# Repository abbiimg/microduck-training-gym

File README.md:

# MicroDuck training gym and design assets

Private working snapshot prepared on **2026-11-01**. This repository contains
MicroDuck CAD, PCB recovery projects, component models, simulation/training
artifacts, audit evidence, and four reusable personal skills.

## Start here

- [Latest package and remaining gaps](MODEL-PLACEMENT-PROGRESS.txt)
- [End-to-end status](END-TO-END-STATUS.txt)
- [17-stage software-check evidence](audit/pcb-tools/software-stack-result.json)
- [Recorded Isaac training run](simulation/validation-runs/2026-10-26_14-57-39_pcb_pipeline_baseline/validation.json)

Recorded checks are dated evidence from the source workstation. The bounded
Isaac run proves integration; it does not establish a reliable walking policy.
Manufacturing and physical reproduction remain unqualified. The canonical
XL330/Feetech choice and revised-IMU copper recovery remain open.

## Clone the published assets

GitHub Desktop supports this repository's Git LFS files. For command-line Git:

```sh
git lfs install
git clone <this-repository-url>
cd microduck-training-gym
git lfs pull
python tools/verify_publication.py
```

Use a Git/LFS clone rather than relying on GitHub's source ZIP. LFS stores CAD,
meshes, archives, media and policy weights separately from their Git pointers.
See [GitHub's LFS documentation](https://docs.github.com/en/repositories/working-with-files/managing-large-files/about-git-large-file-storage).

## Editing and reuse

- `editing/kicad-models-attached/`: five native KiCad review projects with local
  footprint models, assembly STEP/GLB exports and Blender review scenes. Keep
  each complete folder together; models use `${KIPRJMOD}` paths.
- `editing/kicad-cache-repaired/wire_hub_1V0A/`: separate engineering repair of
  the stale GND cache. This revision has no added 3D models; compare its audit.
- `editing/blender/`, `editing/solidworks/`, `community/SolidWorks-XL330-v1.1/`:
  robot meshes, exchange geometry and the community native CAD reconstruction.
- `simulation/`: USD assets and recorded training/export/replay evidence.
- `tools/`: recovery, generation and validation tools. Native KiCad/pcbnew,
  CadQuery/OCP, Blender and the documented WSL Isaac/PCB environments are
  separate prerequisites; their installed runtimes are not embedded here.
- `skills/`: MicroDuck, ECAD/MCAD, Blender/SolidWorks transfer and parametric
  CAD skills. Copy the desired folders into your personal skills directory and
  adapt machine-specific paths and application connections before reuse.

Tracked asset layout and payload bytes are preserved. Reviewed optional payloads are deferred as described below. Many historical scripts and
reports record absolute source-workstation paths. Consult the skill references
for the tested Windows ARM64 / WSL setup rather than assuming those paths exist
on a new machine. Review author/recovered frames before mechanical fit checks.

## Provenance and terms

Selected files from seven pinned source repositories are preserved as **plain file snapshots**, with their
original LICENSE/NOTICE files. [SOURCE-REPOSITORIES.json](SOURCE-REPOSITORIES.json)
records the original URLs and exact commits. Third-party terms remain attached
to each source; there is no blanket license for the whole collection. Robot
mesh derivatives include CC BY-NC-SA 4.0 material; some other source terms are
incomplete. Preserve notices and review rights before any public redistribution.

The original [asset-manifest.json](asset-manifest.json) remains historical
validation evidence, including entries for local caches and optional payloads
omitted from Git. [PUBLICATION-EXCLUSIONS.json](PUBLICATION-EXCLUSIONS.json) and
[DEFERRED-ASSETS.json](DEFERRED-ASSETS.json) document those omissions.
[PUBLICATION-MANIFEST.json](PUBLICATION-MANIFEST.json)
is the hash inventory for the files actually published in this snapshot.

All physical hardware operation, flashing and deployment require a separate
request and validation. No GitHub publication changes the package's recorded
hardware-readiness limits.

## Lean Git publication

See [GITIGNORE-REVIEW.md](GITIGNORE-REVIEW.md) and
[DEFERRED-ASSETS.json](DEFERRED-ASSETS.json). Original CAD release archives,
unused vendor models, optional Rufus binaries and regenerable duplicate exports
stay on the source workstation but are not included in this Git snapshot.
The 57 native working SolidWorks files, baseline Blender scene, current KiCad
model projects, source board STEP files, recovered component geometry, policy
artifacts and known 17-stage verification inputs remain included.

Restore exact deferred files from the retained full package when required:

```sh
python tools/restore_deferred_assets.py --source /path/to/microduck-assets
```

For the original author CAD release ZIP alone, this explicit command downloads
the recorded release and verifies its SHA256:

```sh
python tools/restore_deferred_assets.py --download-original-cad
```

The release ZIP is CAD-only (41 parts and 16 assemblies), with no SolidWorks
program or installer. Fifteen expanded working CAD files differ from that
release; its original URL/hash are retained so both versions remain recoverable.
Some optional export/build tools need deferred inputs restored or regenerated;
the current 17-stage verification receipts retain their known file inputs.

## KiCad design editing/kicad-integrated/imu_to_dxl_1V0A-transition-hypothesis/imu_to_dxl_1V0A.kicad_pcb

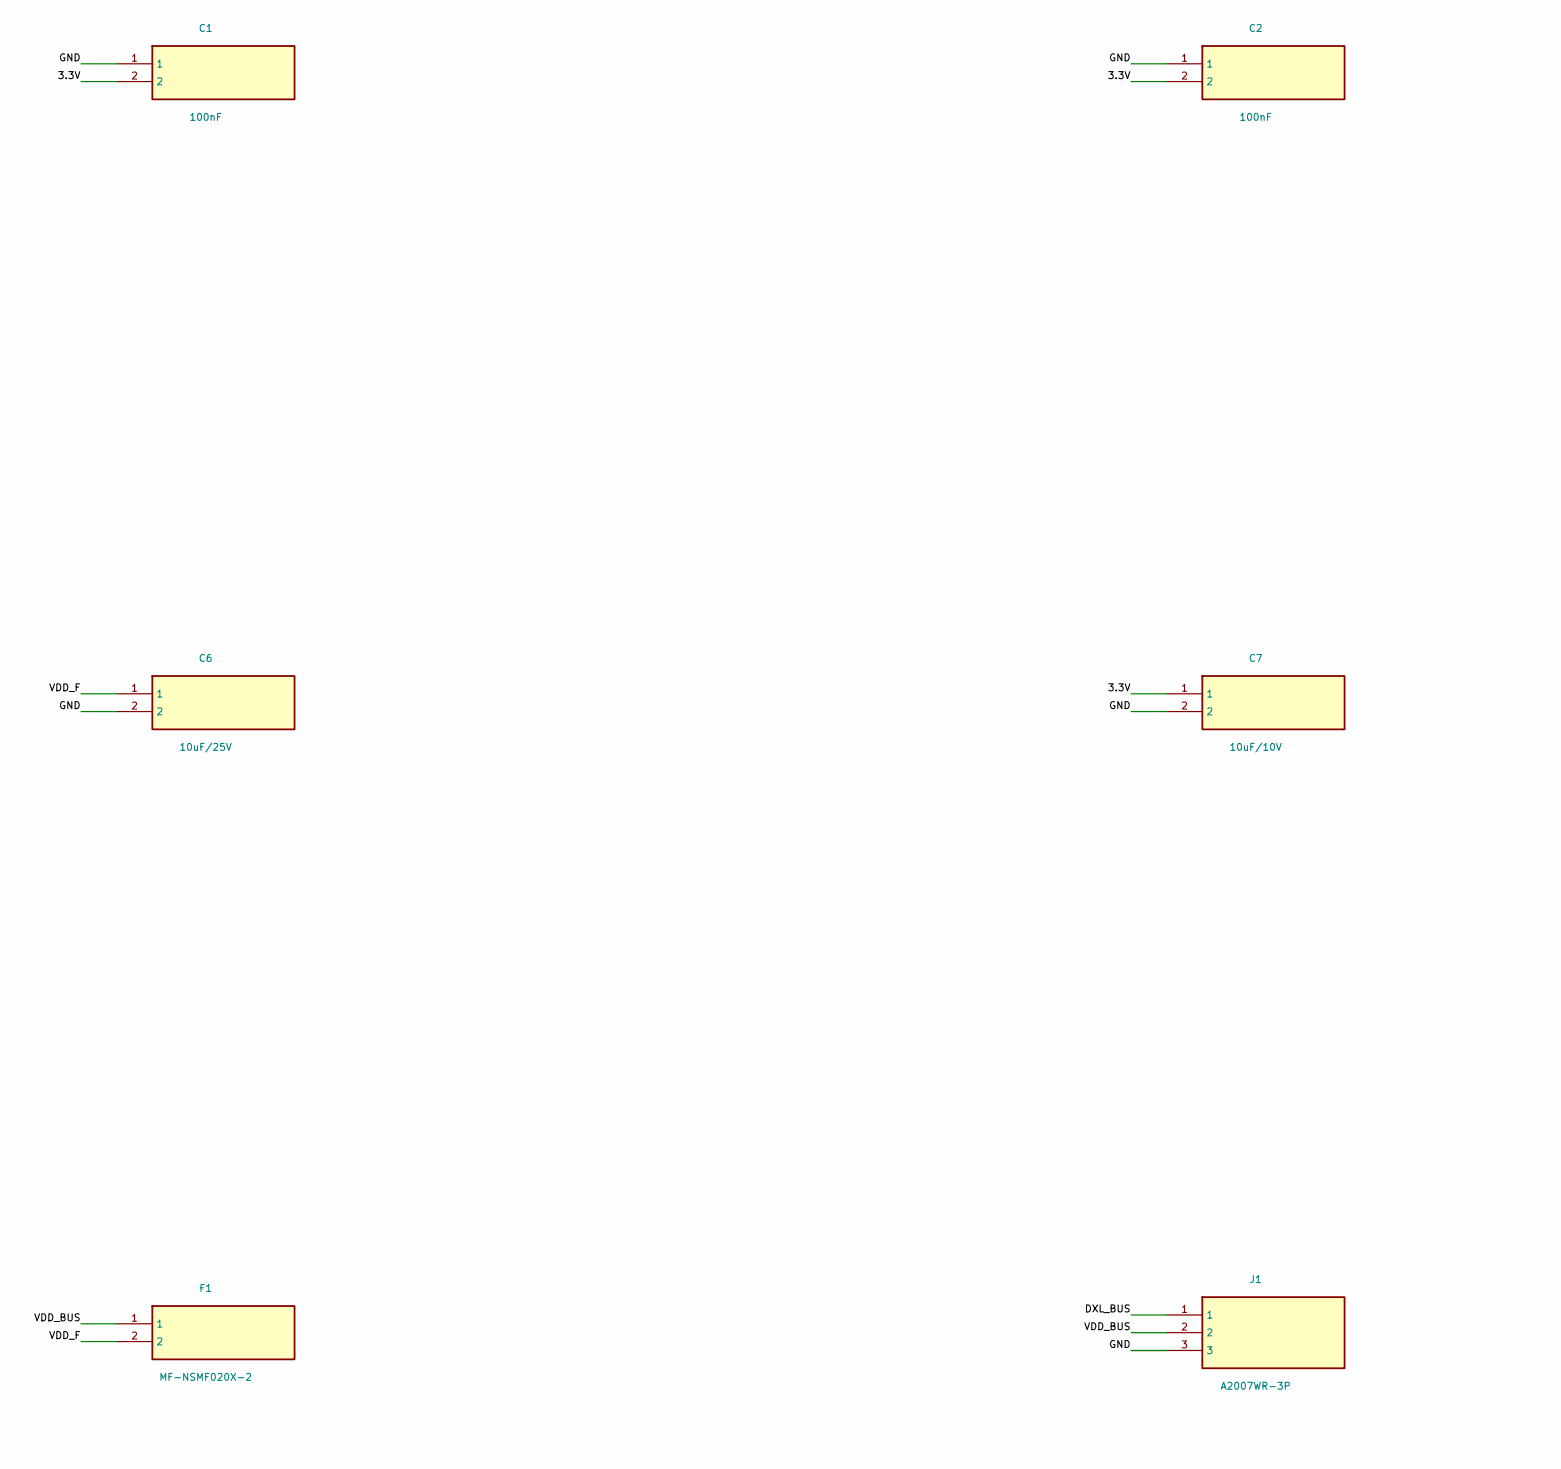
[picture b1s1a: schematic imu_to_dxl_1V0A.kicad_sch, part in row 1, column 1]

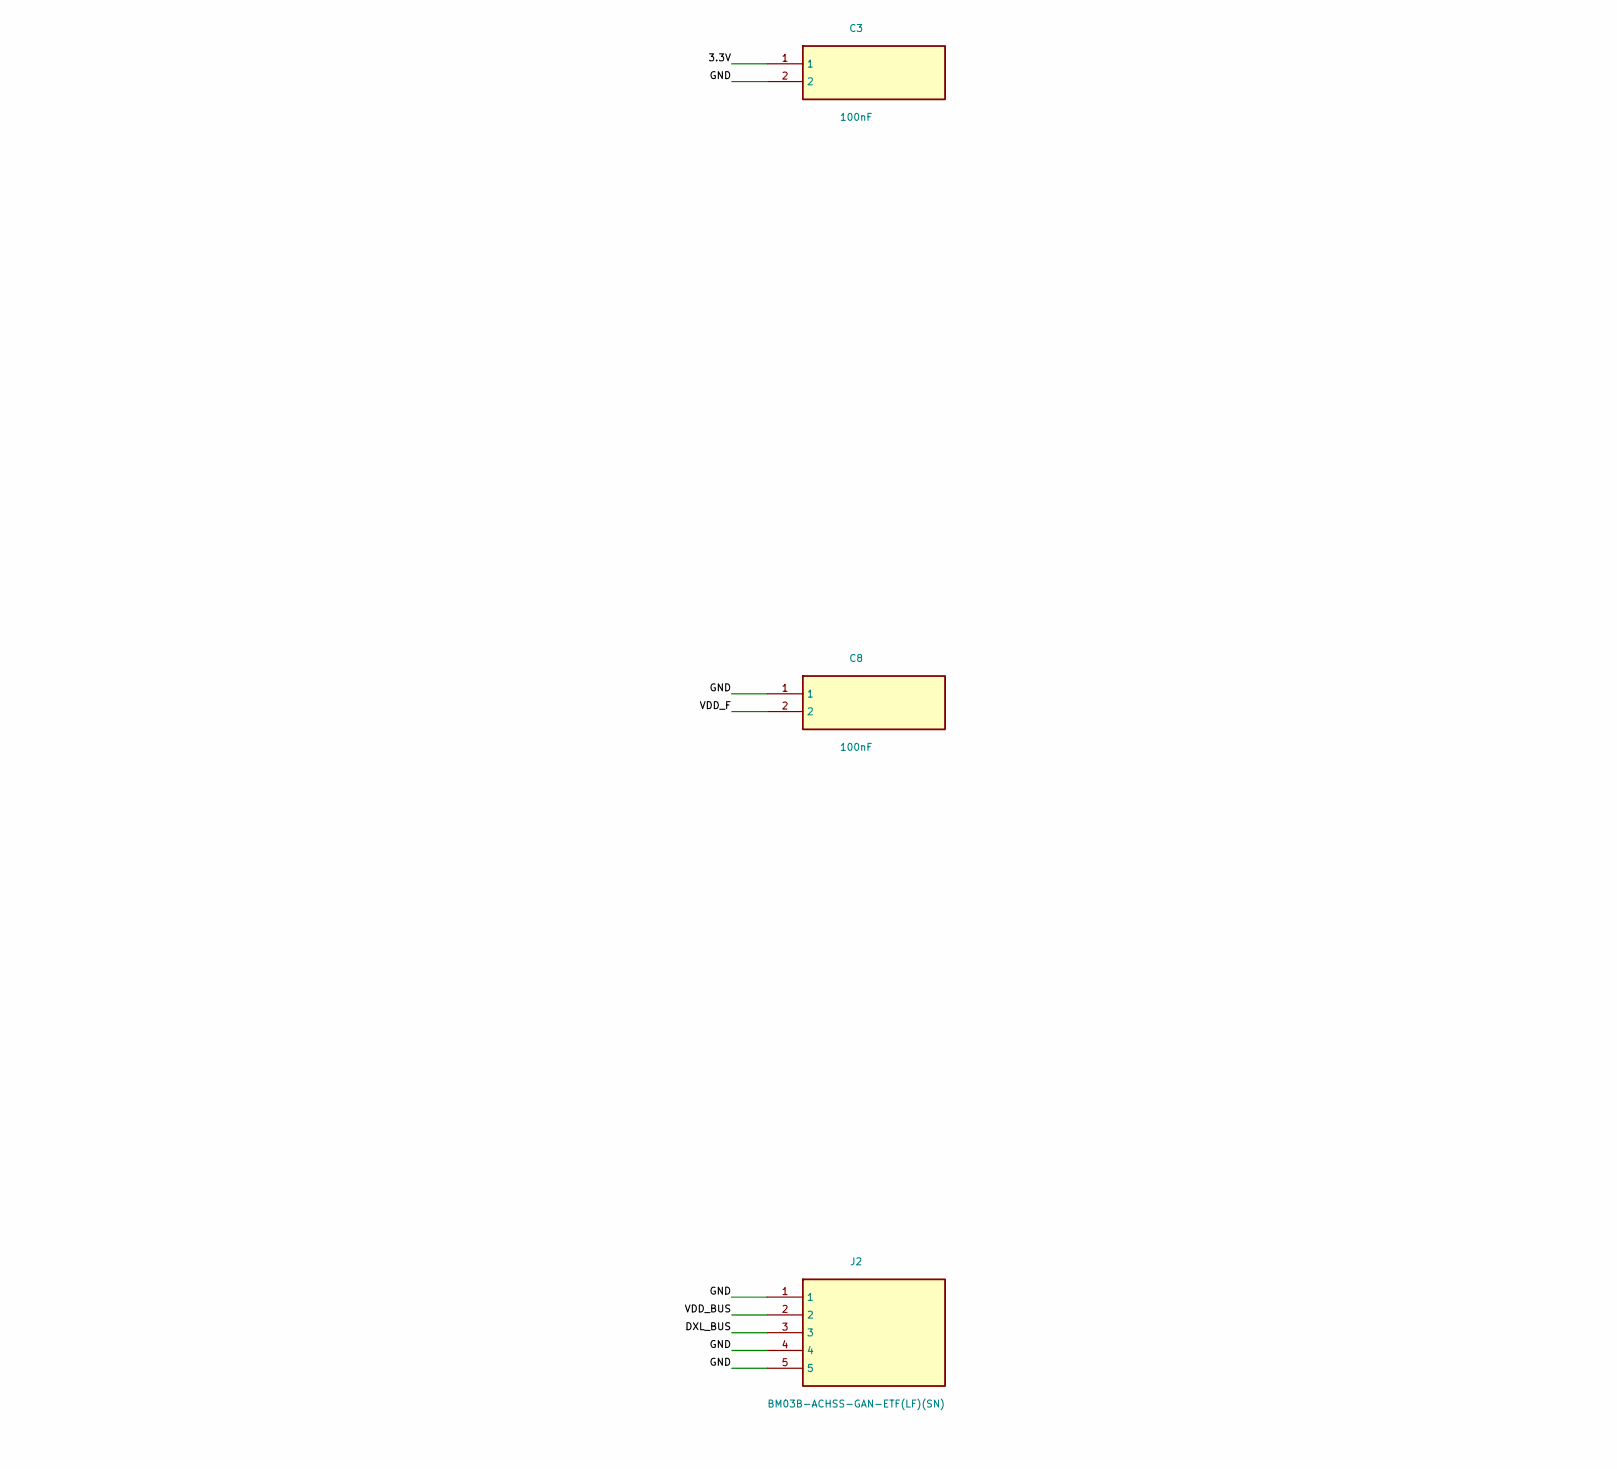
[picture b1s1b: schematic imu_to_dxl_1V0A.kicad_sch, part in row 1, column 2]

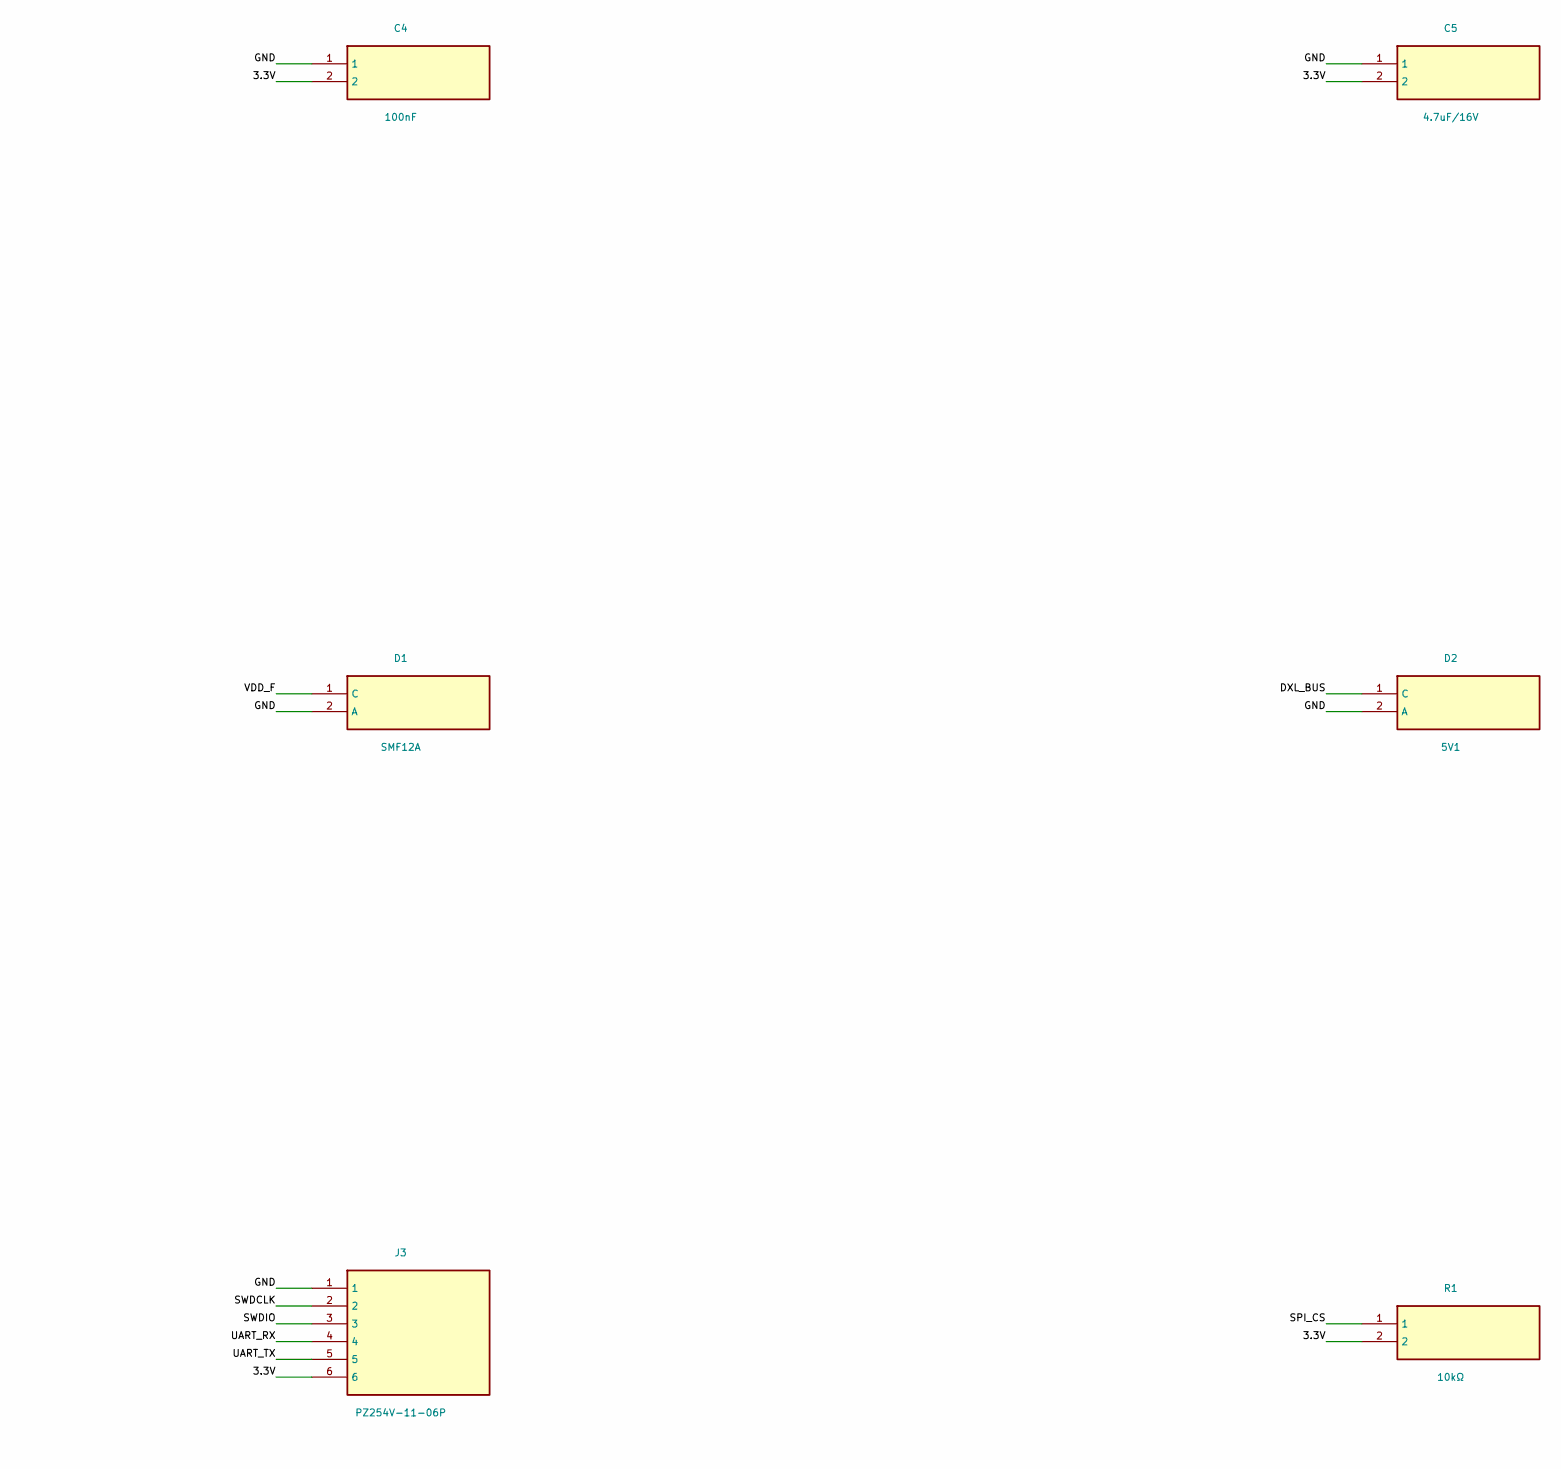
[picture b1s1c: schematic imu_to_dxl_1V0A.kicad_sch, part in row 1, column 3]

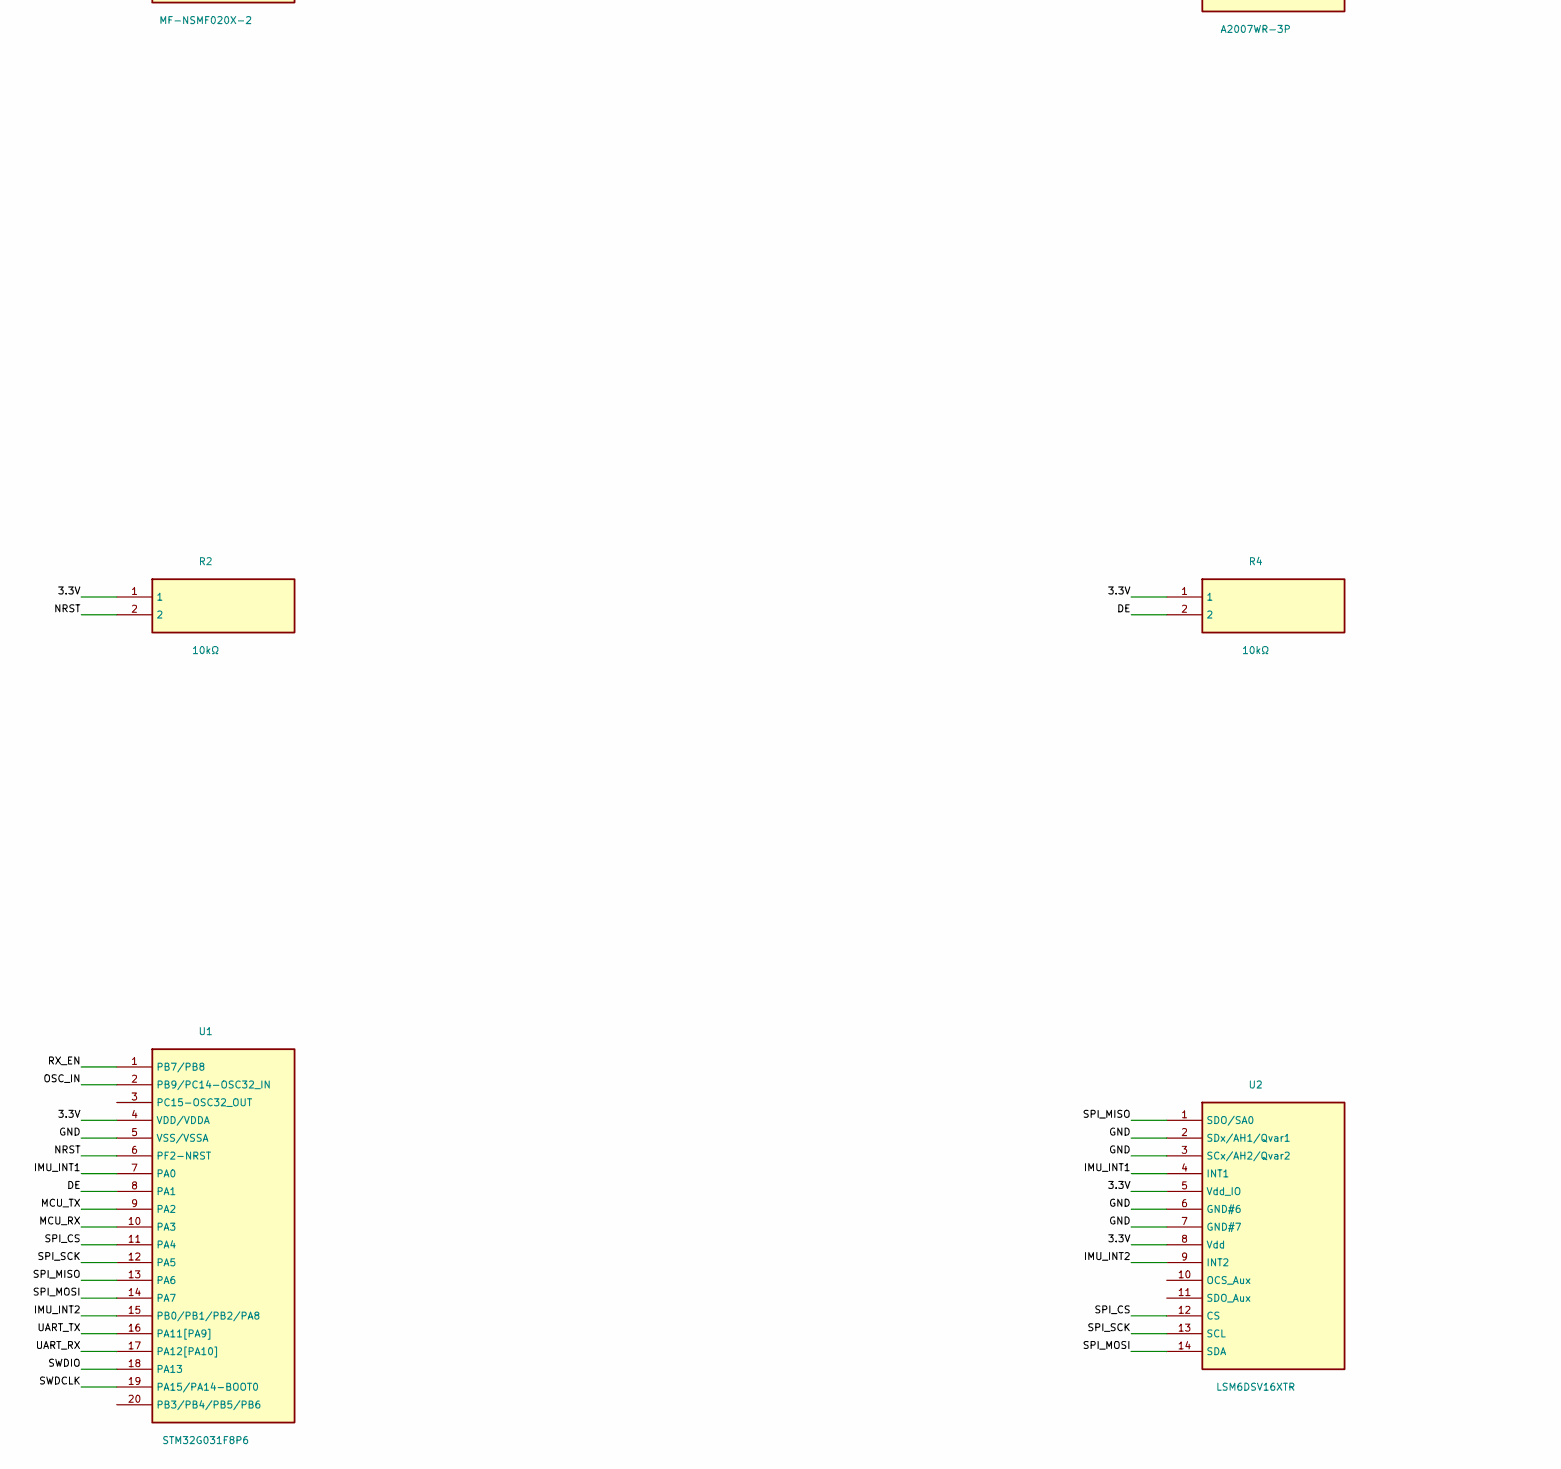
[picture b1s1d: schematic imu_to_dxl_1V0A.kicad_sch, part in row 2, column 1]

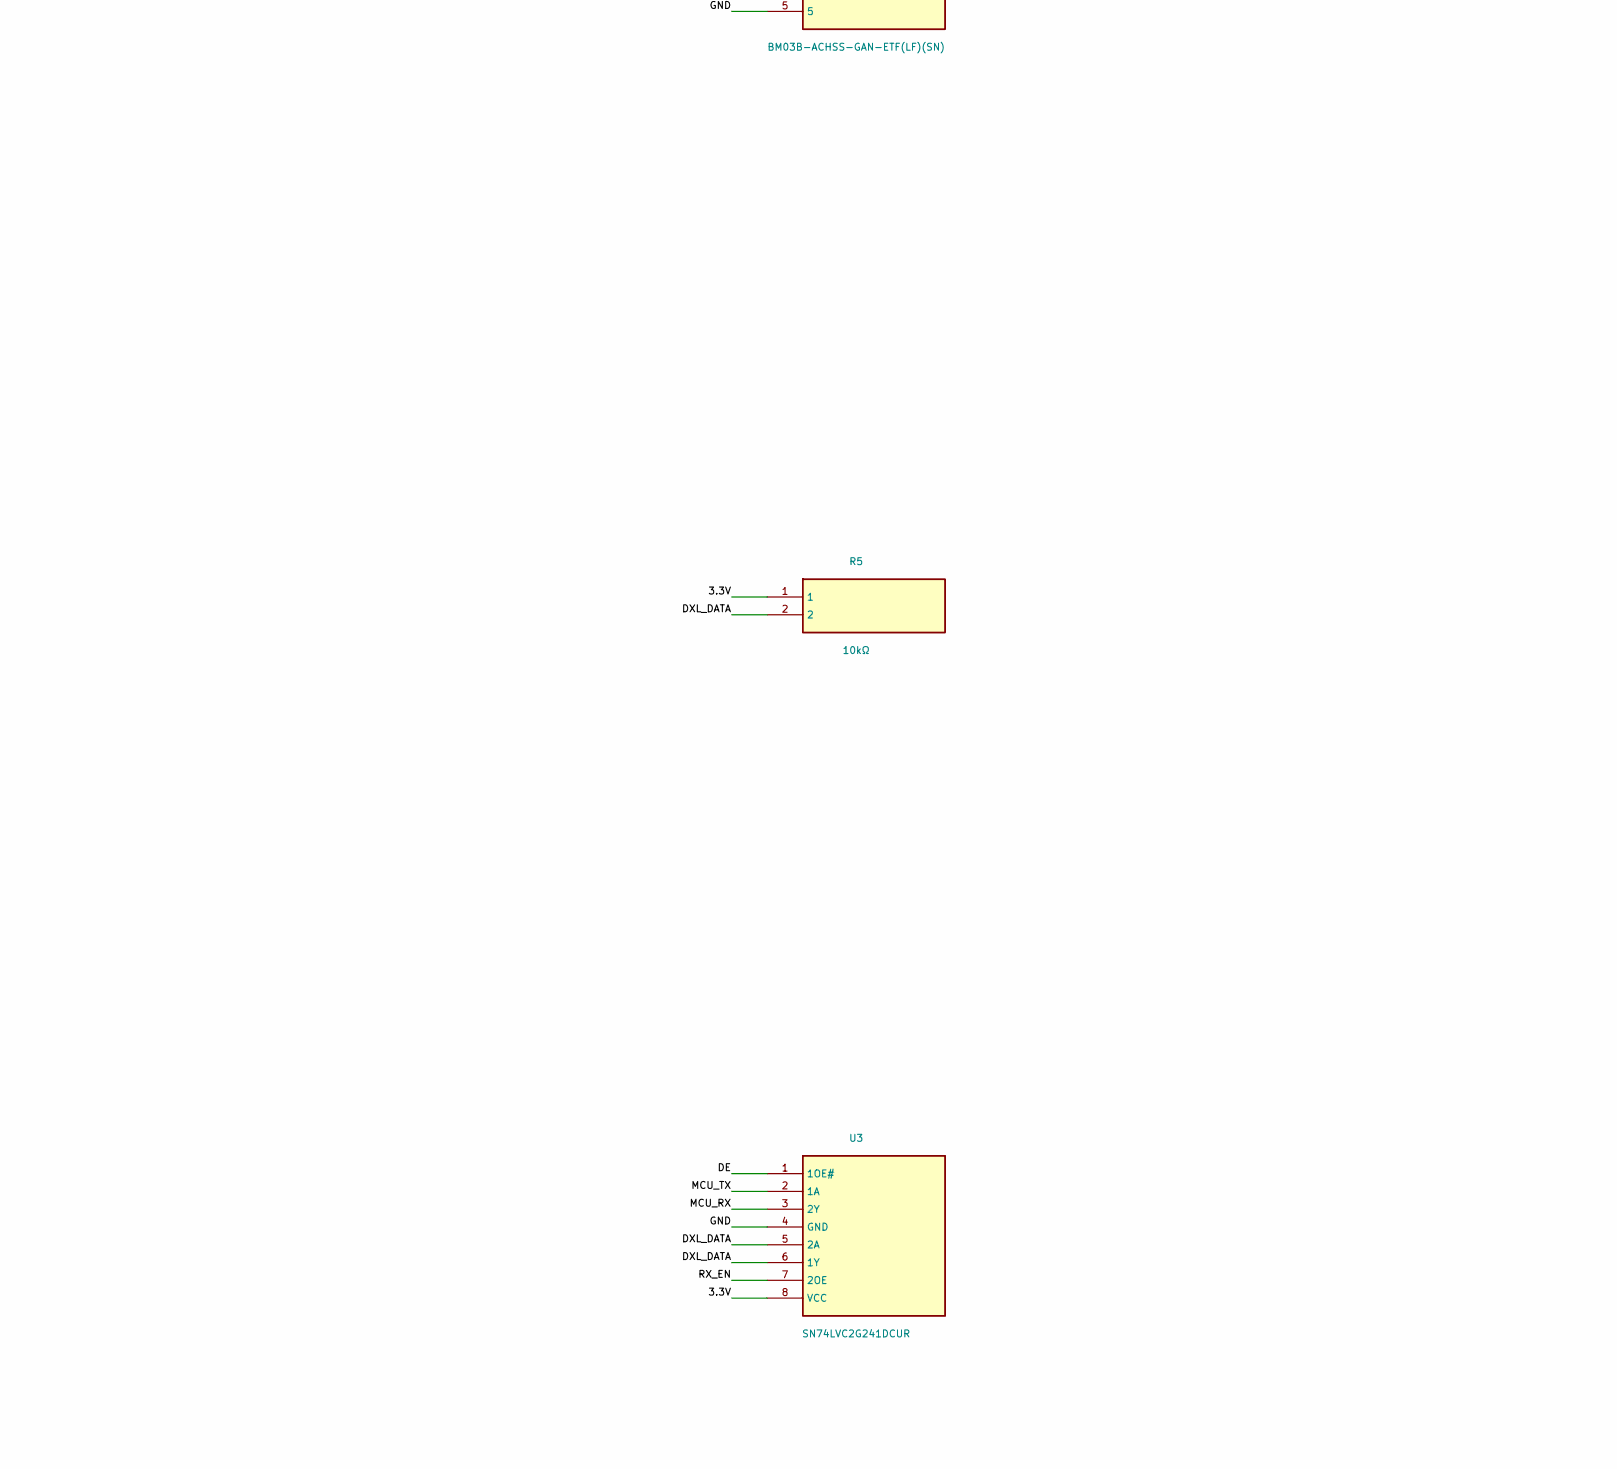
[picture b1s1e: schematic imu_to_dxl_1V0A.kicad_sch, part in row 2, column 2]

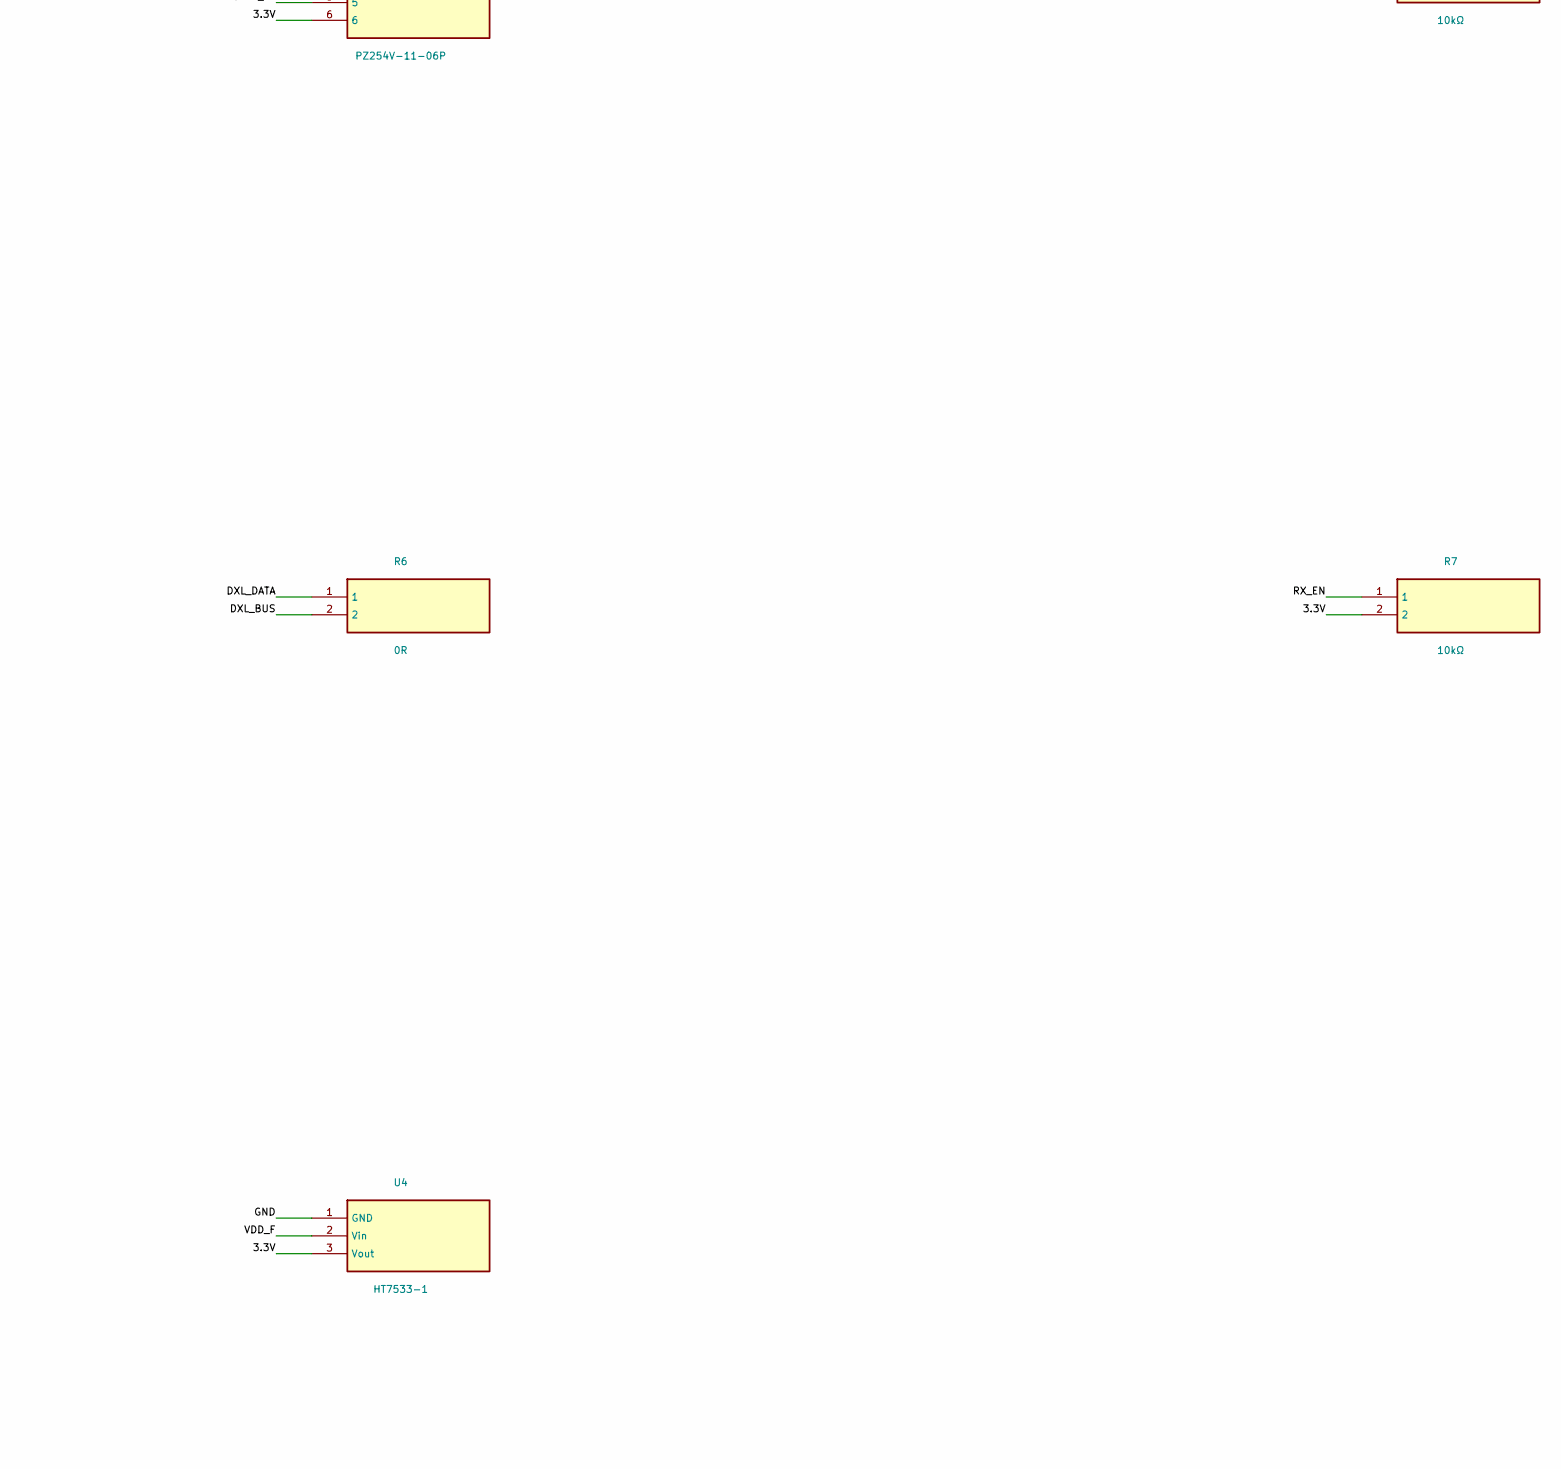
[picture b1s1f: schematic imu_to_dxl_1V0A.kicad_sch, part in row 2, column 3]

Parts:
C1: 100nF; C1; Manufacturer Part CL05B104KO5NNNC; LCSC C1525
C2: 100nF; C2; Manufacturer Part CL05B104KO5NNNC; LCSC C1525
C3: 100nF; C3; Manufacturer Part CL05B104KO5NNNC; LCSC C1525
C4: 100nF; C4; Manufacturer Part CL05B104KO5NNNC; LCSC C1525
C5: 4.7uF/16V; C5; Manufacturer Part CL10A475KO8NNNC; LCSC C19666
C6: 10uF/25V; C6; Manufacturer Part CL21A106KAYNNNE; LCSC C15850
C7: 10uF/10V; C7; Manufacturer Part CL10A106KP8NNNC; LCSC C19702
C8: 100nF; C8; Manufacturer Part CL05B104KO5NNNC; LCSC C1525
D1: SMF12A; D1; Manufacturer Part SMF12A; LCSC C2943870
D2: 5V1; D2; Manufacturer Part BZT52C5V1-7-F; LCSC C151588
F1: MF-NSMF020X-2; F1; Manufacturer Part MF-NSMF020X-2; LCSC C210358
J1: A2007WR-3P; J1; Manufacturer Part A2007WR-3P; LCSC C225350
J2: BM03B-ACHSS-GAN-ETF(LF)(SN); J2; Manufacturer Part BM03B-ACHSS-GAN-ETF(LF)(SN); LCSC C5118705
J3: PZ254V-11-06P; J3; Manufacturer Part PZ254V-11-06P; LCSC C492405
R1: 10kΩ; R1; Manufacturer Part RC0402FR-0710KL; LCSC C60490
R2: 10kΩ; R2; Manufacturer Part RC0402FR-0710KL; LCSC C60490
R4: 10kΩ; R4; Manufacturer Part RC0402FR-0710KL; LCSC C60490
R5: 10kΩ; R5; Manufacturer Part RC0402FR-0710KL; LCSC C60490
R6: 0R; R6; Manufacturer Part 0603WAF0000T5E; LCSC C21189
R7: 10kΩ; R7; Manufacturer Part RC0402FR-0710KL; LCSC C60490
U1: STM32G031F8P6; U1; Manufacturer Part STM32G031F8P6; LCSC C529334
U2: LSM6DSV16XTR; U2; Manufacturer Part LSM6DSV16XTR; LCSC C5267406
U3: SN74LVC2G241DCUR; U3; Manufacturer Part SN74LVC2G241DCUR; LCSC C10430
U4: HT7533-1; U4; Manufacturer Part HT7533-1; LCSC C14289

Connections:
/3.3V: C1.2, C2.2, C3.1, C4.2, C5.2, C7.1, J3.6, R1.2, R2.1, R4.1, R5.1, R7.2, U1.4 (VDD/VDDA), U2.5 (Vdd_IO), U2.8 (Vdd), U3.8 (VCC), U4.3 (Vout)
/DE: R4.2, U1.8 (PA1), U3.1 (1OE#)
/DXL_BUS: D2.1 (C), J1.1, J2.3, R6.2
/DXL_DATA: R5.2, R6.1, U3.5 (2A), U3.6 (1Y)
/GND: C1.1, C2.1, C3.2, C4.1, C5.1, C6.2, C7.2, C8.1, D1.2 (A), D2.2 (A), J1.3, J2.1, J2.4, J2.5, J3.1, U1.5 (VSS/VSSA), U2.2 (SDx/AH1/Qvar1), U2.3 (SCx/AH2/Qvar2), U2.6 (GND#6), U2.7 (GND#7), U3.4 (GND), U4.1 (GND)
/IMU_INT1: U1.7 (PA0), U2.4 (INT1)
/IMU_INT2: U1.15 (PB0/PB1/PB2/PA8), U2.9 (INT2)
/MCU_RX: U1.10 (PA3), U3.3 (2Y)
/MCU_TX: U1.9 (PA2), U3.2 (1A)
/NRST: R2.2, U1.6 (PF2-NRST)
/OSC_IN: U1.2 (PB9/PC14-OSC32_IN)
/RX_EN: R7.1, U1.1 (PB7/PB8), U3.7 (2OE)
/SPI_CS: R1.1, U1.11 (PA4), U2.12 (CS)
/SPI_MISO: U1.13 (PA6), U2.1 (SDO/SA0)
/SPI_MOSI: U1.14 (PA7), U2.14 (SDA)
/SPI_SCK: U1.12 (PA5), U2.13 (SCL)
/SWDCLK: J3.2, U1.19 (PA15/PA14-BOOT0)
/SWDIO: J3.3, U1.18 (PA13)
/UART_RX: J3.4, U1.17 (PA12[PA10])
/UART_TX: J3.5, U1.16 (PA11[PA9])
/VDD_BUS: F1.1, J1.2, J2.2
/VDD_F: C6.1, C8.2, D1.1 (C), F1.2, U4.2 (Vin)

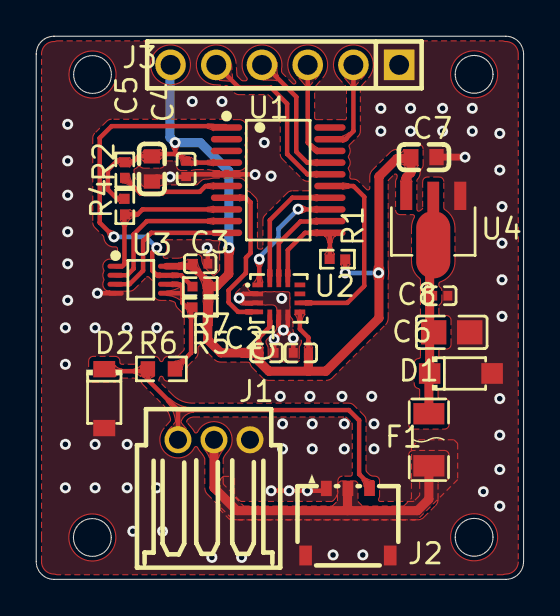
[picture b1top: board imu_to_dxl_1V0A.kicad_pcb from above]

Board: 2 copper layers, 27.1 x 30.2 mm, 24 parts (0 on the bottom side), 21 nets.

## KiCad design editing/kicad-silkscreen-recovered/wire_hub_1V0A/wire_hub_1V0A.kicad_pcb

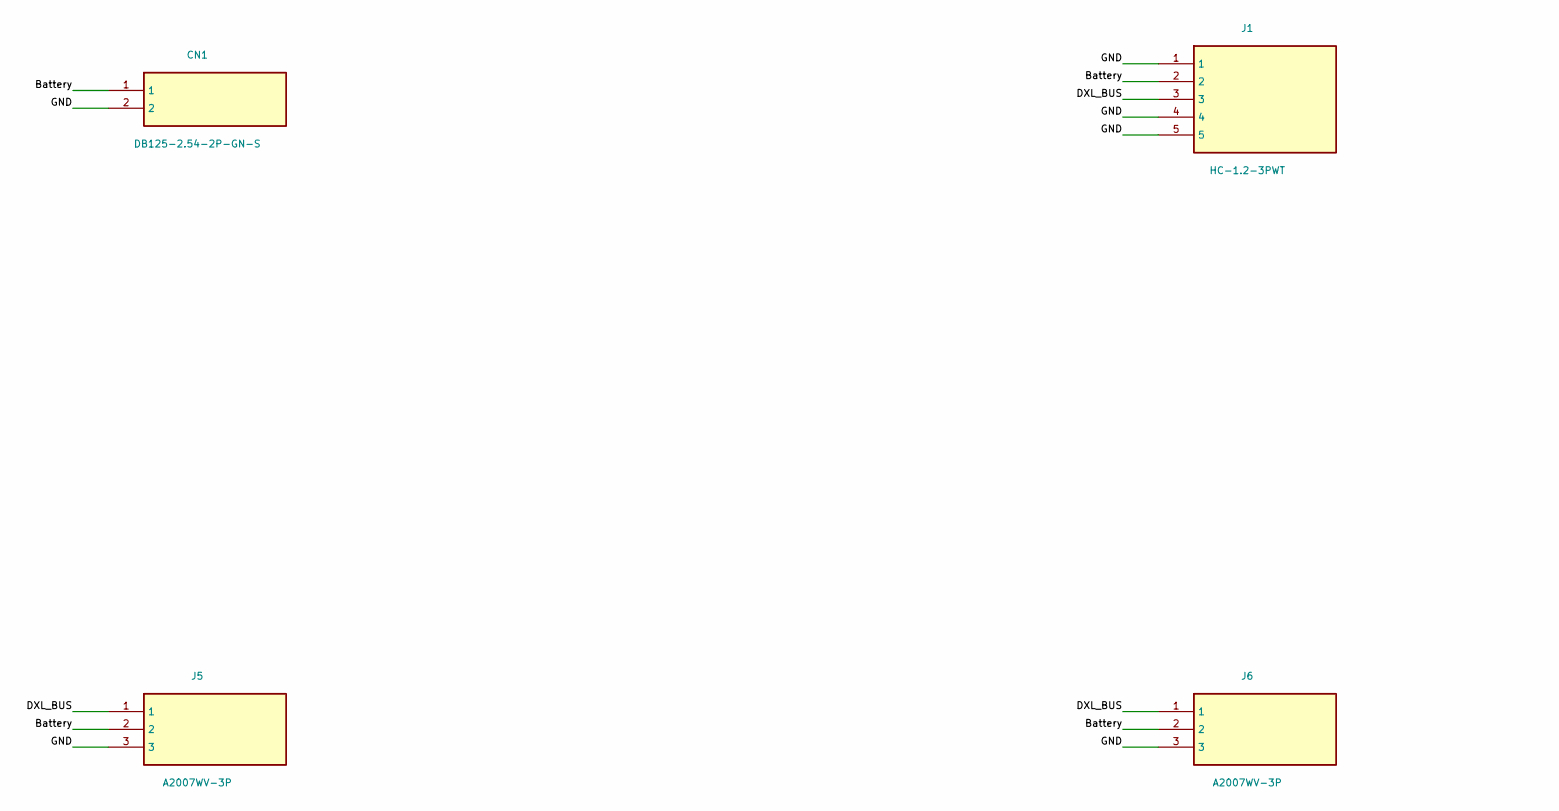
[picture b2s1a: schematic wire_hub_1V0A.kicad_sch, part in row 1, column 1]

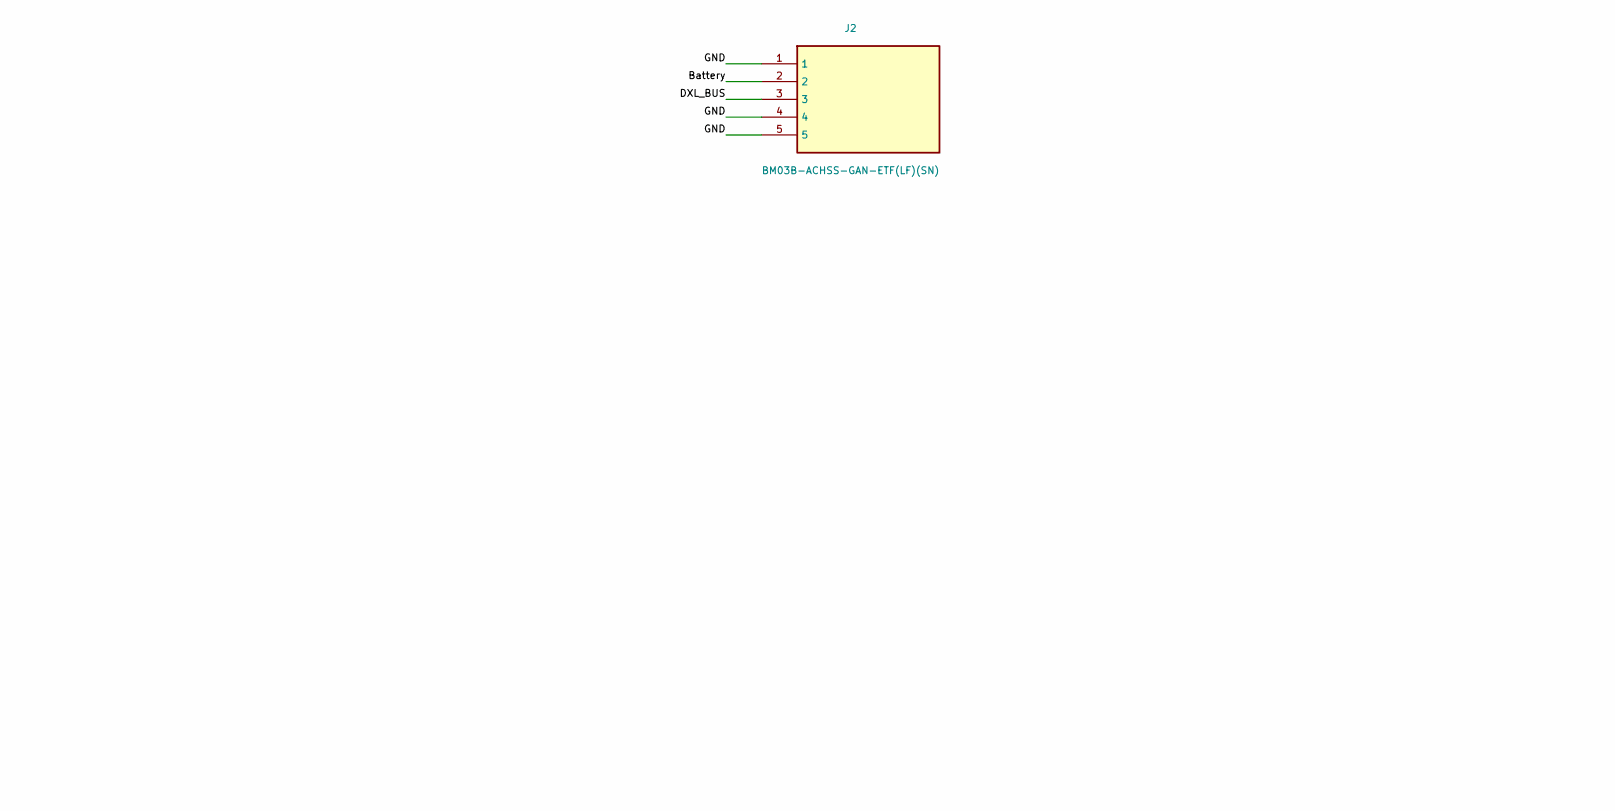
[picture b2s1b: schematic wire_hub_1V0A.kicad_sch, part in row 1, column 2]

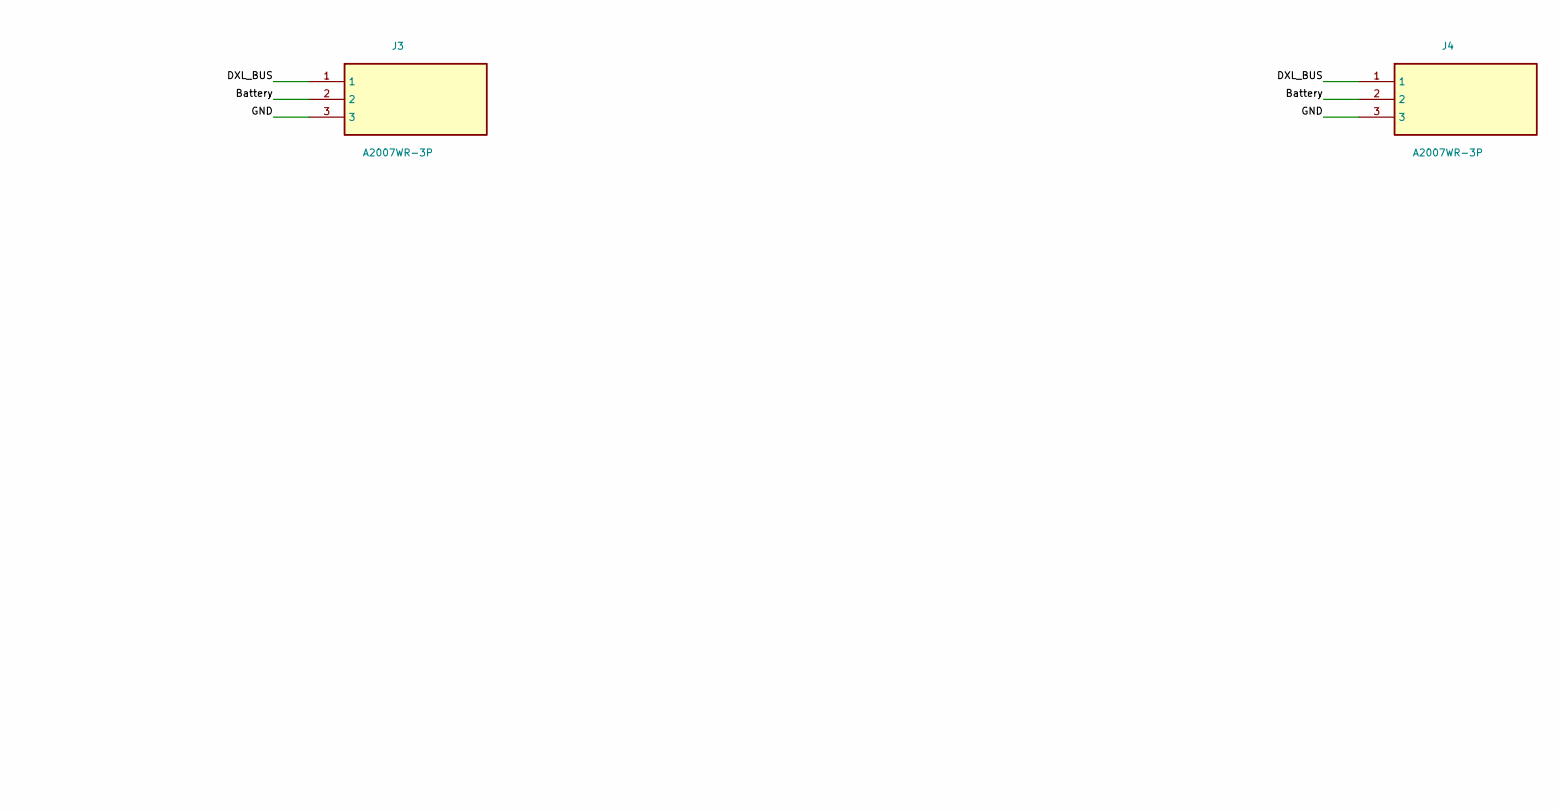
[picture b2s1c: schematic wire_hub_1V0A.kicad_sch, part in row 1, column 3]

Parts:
CN1: DB125-2.54-2P-GN-S; CN1
J1: HC-1.2-3PWT; J1; Manufacturer Part HC-1.2-3PWT; LCSC C2997426
J2: BM03B-ACHSS-GAN-ETF(LF)(SN); J2; Manufacturer Part BM03B-ACHSS-GAN-ETF(LF)(SN); LCSC C5118705
J3: A2007WR-3P; J3; Manufacturer Part A2007WR-3P; LCSC C225350
J4: A2007WR-3P; J4; Manufacturer Part A2007WR-3P; LCSC C225350
J5: A2007WV-3P; J5; Manufacturer Part A2007WV-3P; LCSC C225336
J6: A2007WV-3P; J6; Manufacturer Part A2007WV-3P; LCSC C225336

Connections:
/Battery: CN1.1, J1.2, J2.2, J3.2, J4.2, J5.2, J6.2
/DXL_BUS: J1.3, J2.3, J3.1, J4.1, J5.1, J6.1
/GND: CN1.2, J1.1, J1.4, J1.5, J2.1, J2.4, J2.5, J3.3, J4.3, J5.3, J6.3

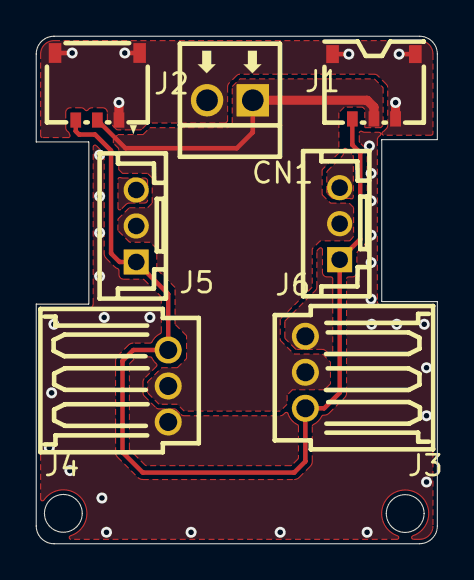
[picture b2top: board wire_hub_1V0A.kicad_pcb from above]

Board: 2 copper layers, 22.3 x 28.2 mm, 7 parts (0 on the bottom side), 3 nets.
